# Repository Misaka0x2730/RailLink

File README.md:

# RailLink
Very compact isolated version of J-Link v9 with fully supported functions. </br>
Isolation based on ADuM4160 (USB2.0 FS isolation) and B0505S-1W (Isolated 5V/0.2A DC-DC). </br>

# Overview
Dimensions(L x W x H, millimeters): 70 x 28 x 15 (probe only); 110 x 35 x 25 (probe with connected adapter). </br>

# Probe pinout
RailLink has 10 pin 0.1"(2.54mm) connector compatible with standard ARM 10 pin connector.

<b>RailLink connector</b></br>

|Pin|Name   |Pin|Name        |
|---|-------|---|------------|
|1  |Vtref  |2  | TMS/SWDIO  |
|3  |GND    |4  | TCK/SWCLK  |
|5  |GND    |6  | TDO/SWO    |
|7  |UART RX|8  | TDI/UART TX|
|9  |GND    |10 | ~RESET     |

# Adapter pinouts
Adapter has several popular connectors: ARM 10 pin 0.05"(1.27mm), TC2030-IDC-NL  6 pin 0.1"(2.54mm), ARM 20 pin JTAG 0.1"(2.54mm), ARM 20-pin Cortex 0.05"(1.27mm). </br>
In addition, there are two custom connectors: 4 pin UART and CWF-6 (Ilya).

<b>ARM 10 pin 0.05"(1.27mm)</b></br>

|Pin|Name   |Pin|Name        |
|---|-------|---|------------|
|1  |Vtref  |2  | TMS/SWDIO  |
|3  |GND    |4  | TCK/SWCLK  |
|5  |GND    |6  | TDO/SWO    |
|7  |UART RX|8  | TDI/UART TX|
|9  |GND    |10 | ~RESET     |

</br></br><b>TC2030-IDC-NL</b></br>

|Pin|Name   |Pin|Name        |
|---|-------|---|------------|
|1  |Vtref  |2  | TMS/SWDIO  |
|3  |~RESET |4  | TCK/SWCLK  |
|5  |GND    |6  | TDO/SWO    |

</br></br><b>ARM 20 pin JTAG 0.1"(2.54mm)</b></br>

|Pin|Name        |Pin|Name |
|---|------------|---|-----|
|1  |Vtref       |2  | NC  |
|3  |NC          |4  | GND |
|5  |TDI/UART TX |6  | GND |
|7  |TMS/SWDIO   |8  | GND |
|9  |TCK/SWCLK   |10 | GND |
|11 |NC          |12 | GND |
|13 |TDO/SWO     |14 | GND |
|15 |~RESET      |16 | GND |
|17 |UART RX     |18 | GND |
|19 |NC          |20 | GND |

</br></br><b>ARM 20-pin Cortex 0.05"(1.27mm)</b></br>

|Pin|Name   |Pin|Name        |
|---|-------|---|------------|
|1  |Vtref  |2  | TMS/SWDIO  |
|3  |GND    |4  | TCK/SWCLK  |
|5  |GND    |6  | TDO/SWO    |
|7  |UART RX|8  | TDI/UART TX|
|9  |GND    |10 | ~RESET     |
|11 |GND    |12 | NC         |
|13 |GND    |14 | NC         |
|15 |GND    |16 | NC         |
|17 |GND    |18 | NC         |
|19 |GND    |20 |NC          |

</br></br><b>4 pin UART</b></br>

|Pin|Name        |
|---|------------|
|1  |Vtref       |
|2  |TDI/UART TX |
|3  |UART RX     |
|4  |GND         |

</br></br><b>CWF-6 (Ilya)</b></br>

|Pin|Name        |
|---|------------|
|1  |Vtref       |
|2  |TCK/SWCLK   |
|3  |TMS/SWDIO   |
|4  |~RESET      |
|3  |UART RX     |
|4  |GND         |

# Assembly
Most of SMD components are 0402. </br> 
Assembly should be not very difficult even with soldering iron. </br>
But paste soldering with stencil is recommended. </br>
Assembly drawing placed [here](https://github.com/Misaka0x2730/RailLink/blob/master/BOM/ibom.html). </br>
Assembly drawing should be opened in browser. </br>

# Programming
 1. Install J-Link software pack.
 2. Load the bootloader
    * <b>ST-LINK way </b>
      1. Install ST-LINK utility
      2. Connect RailLink SWD connector to ST-LINK
      3. Connect ST-LINK to PC
      4. Connect RailLink to PC
      5. Launch ST-LINK utility
      6. Load [this file](https://github.com/Kevincoooool/KS_Diy_Link/blob/master/Jlink_V9/%E5%9B%BA%E4%BB%B6%E5%8D%87%E7%BA%A7%E6%96%B9%E5%BC%8F/JLink-v9_bootloader%E5%9B%BA%E4%BB%B6/bootloader.bin)
      into MCU.
    * <b>J-Link way</b>
      1. Connect RailLink SWD connector to J-Link
      2. Connect J-Link to PC
      3. Connect RailLink to PC
      4. Start JFlashLite </br> 
      6. Select device - STM32F205RC, select interface - SWD, and speed - 100kHz </br>
      
      8. In Data file field choose [this file](https://github.com/Kevincoooool/KS_Diy_Link/blob/master/Jlink_V9/%E5%9B%BA%E4%BB%B6%E5%8D%87%E7%BA%A7%E6%96%B9%E5%BC%8F/JLink-v9_bootloader%E5%9B%BA%E4%BB%B6/bootloader.bin)
      9. Click "Program Device" button
      10. Wait until the firmware is loaded;
  3. Disconnect RailLink and JLink from PC.
  4. Connect RailLink to PC.
  5. Launch JLink.exe (JLinkExe on Linux) and agree to firmware restoring.
  6. Wait until firmware is restored.
  7. Now RailLink is almost ready for use. Type and run "Exec SetSN=xxxxxxxx", where xxxxxxxx is serial number; 
  8. <b> RailLink is ready for use! </b>
  
<b>PS. Important! </b></br> It's recommended to add following options:
  * Exec AddFeature GDB
  * Exec AddFeature RDI
  * Exec AddFeature FlashBP
  * Exec AddFeature FlashDL
  * Exec AddFeature JFlash
  * Exec AddFeature RDDI </br>
But in latest version (V6.80 at this moment) any of these commands causes "ERROR: Unknown command". </br>
You can install older version (two or more version of JLink software pack can be install on one PC) and try to execute these commands. 
For example, it's working on V6.30.

# License
 </br>
This project is licensed under a [CERN Open Hardware Licence Version 2 - Permissive](https://ohwr.org/cern_ohl_p_v2.pdf).

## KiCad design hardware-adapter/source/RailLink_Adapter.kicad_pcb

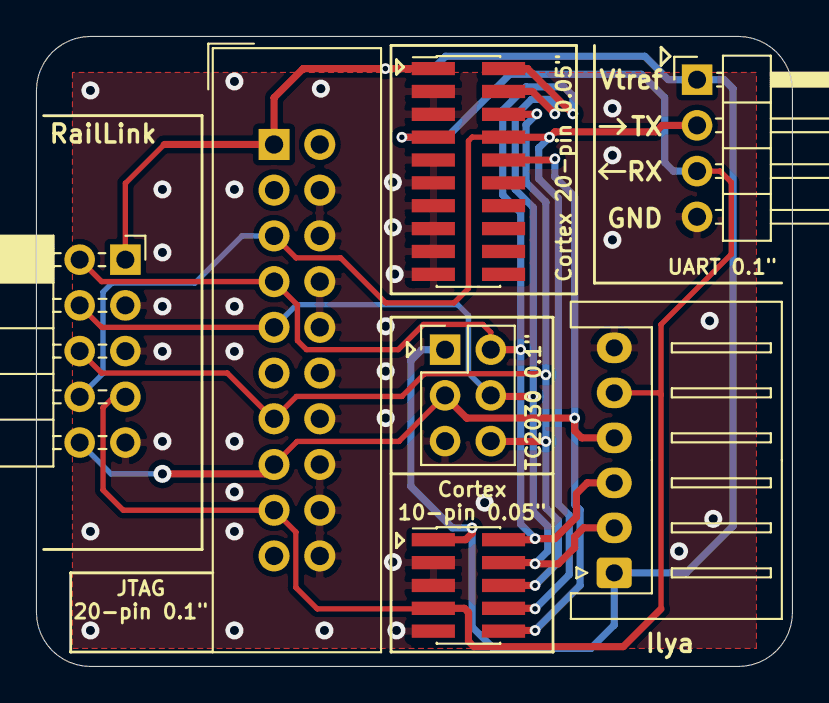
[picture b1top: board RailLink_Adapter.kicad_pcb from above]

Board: 2 copper layers, 42.0 x 35.0 mm, 7 parts (0 on the bottom side), 8 nets.

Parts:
J1: RailLink; PinSocket_2x05_P2.54mm_Horizontal
J2: 10-pin Cortex Debug; PinHeader_2x05_P1.27mm_Vertical_SMD
J3: TC2030-IDC-NL; PinHeader_2x03_P2.54mm_Vertical
J4: Standard JTAG; IDC-Header_2x10_P2.54mm_Vertical
J5: 20-pin Cortex Debug + ETM; PinHeader_2x10_P1.27mm_Vertical_SMD
J6: UART; PinHeader_1x04_P2.54mm_Horizontal
J7: Ilya; JST_XH_S6B-XH-A_1x06_P2.50mm_Horizontal

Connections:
/RXD: J1.7, J2.7, J4.17, J5.7, J6.3, J7.5
/TCK: J1.4, J2.4, J3.4, J4.9, J5.4, J7.2
/TDI: J1.8, J2.8, J4.5, J5.8, J6.2
/TDO: J1.6, J2.6, J3.6, J4.13, J5.6
/TMS: J1.2, J2.2, J3.2, J4.7, J5.2, J7.3
/Vtref: J1.1, J2.1, J3.1, J4.1, J5.1, J6.1, J7.1
/~RESET: J1.10, J2.10, J3.3, J4.15, J5.10, J7.4
GND: J1.3, J1.5, J1.9, J2.3, J2.5, J2.9, J3.5, J4.4, J4.6, J4.8, J4.10, J4.12, J4.14, J4.16, J4.18, J4.20, J5.3, J5.5, J5.9, J5.11, J5.13, J5.15, J5.17, J5.19, J6.4, J7.6

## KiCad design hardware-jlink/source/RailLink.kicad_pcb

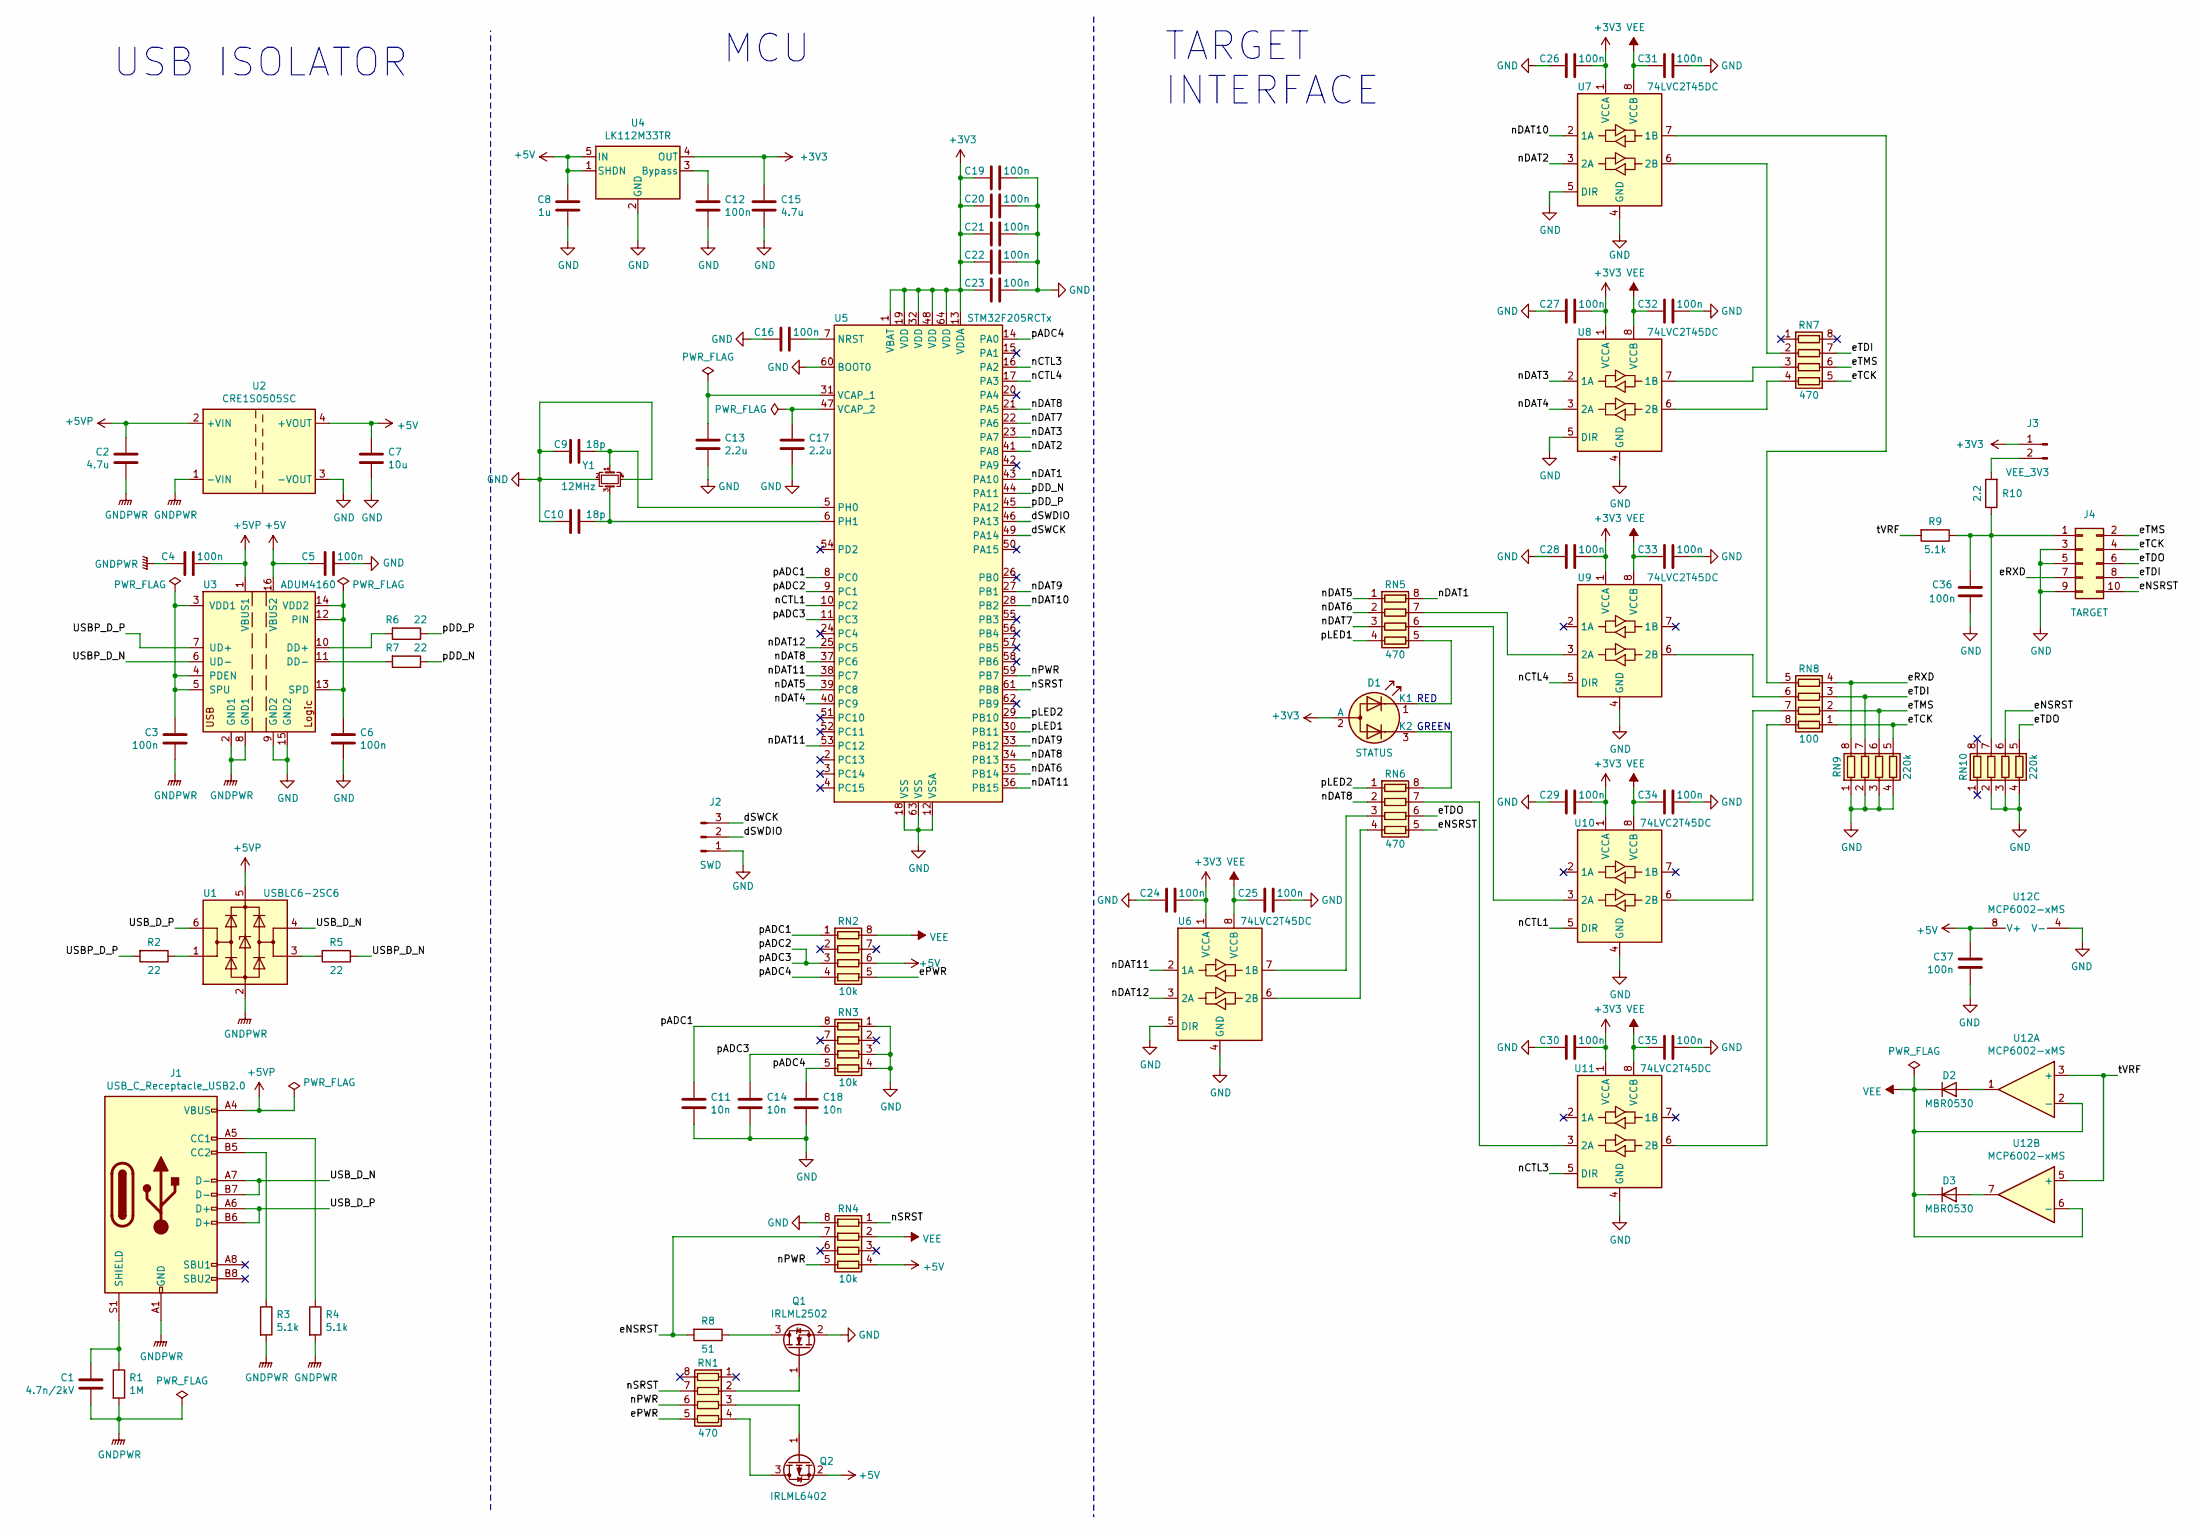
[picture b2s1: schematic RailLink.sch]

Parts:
C1: 4.7n/2kV; C_1812_4532Metric; Part Number 202S43W472KV4E
C2, C15: 4.7u; C_0603_1608Metric; Part Number CL10A475KP8NNNC
C3, C4, C5, C6, C12, C16, C19, C20, C21, C22, C23, C24, C25, C26, C27, C28, C29, C30, C31, C32, C33, C34, C35, C36, C37: 100n; C_0402_1005Metric; Part Number 0402B104K160CT
C7: 10u; C_0603_1608Metric; Part Number GRM188R61A106ME69D
C8: 1u; C_0603_1608Metric; Part Number CL10B105KP8NNNC
C9, C10: 18p; C_0402_1005Metric; Part Number C1005NP0180KGT
C11, C14, C18: 10n; C_0402_1005Metric; Part Number 0402B103K500NT
C13, C17: 2.2u; C_0603_1608Metric; Part Number CL10A225KP8NNNC
D1: STATUS; LED_D3.0mm-3; Part Number TJ-L3FYTXHMCYLC2R2G-A5
D2, D3: MBR0530; D_SOD-123; Part Number MBR0530
J1: USB_C_Receptacle_USB2.0; USB_C_Receptacle_HRO_TYPE-C-31-M-12; Part Number TYPE-C-31-M-12
J2: SWD; PinHeader_1x03_P2.54mm_Vertical; Part Number C2337
J3: VEE_3V3; PinHeader_1x02_P2.54mm_Vertical; Part Number C2337
J4: TARGET; IDC-Header_2x05_P2.54mm_Horizontal; Part Number C9140
Q1: IRLML2502; SOT-23; Part Number IRLML2502
Q2: IRLML6402; SOT-23; Part Number IRLML6402
R1: 1M; R_1206_3216Metric; Part Number 1206W4J0105T5E
R2, R5, R6, R7: 22; R_0402_1005Metric; Part Number 0402WGF220JTCE
R3, R4, R9: 5.1k; R_0402_1005Metric; Part Number 0402WGJ0512TCE
R8: 51; R_0402_1005Metric; Part Number 0402WGJ0510TCE
R10: 2.2; R_0402_1005Metric; Part Number RC0402FR-071KL
RN1, RN5, RN6, RN7: 470; R_Array_Concave_4x0603; Part Number 4D03WGJ0471T5E
RN2, RN3, RN4: 10k; R_Array_Concave_4x0603; Part Number 4D03WGJ0103T5E
RN8: 100; R_Array_Concave_4x0603; Part Number 4D03WGJ0101T5E
RN9, RN10: 220k; R_Array_Concave_4x0603; Part Number 4D03WGJ0224T5E
U1: USBLC6-2SC6; SOT-23-6; Part Number USBLC6-2SC6
U2: CRE1S0505SC; Converter_DCDC_muRata_CRE1xxxxxxSC_THT; Part Number B0505S-1W
U3: ADUM4160; SOIC-16W_7.5x10.3mm_P1.27mm; Part Number ADUM4160BRWZ-RL
U4: LK112M33TR; SOT-23-5; Part Number LK112M33TR
U5: STM32F205RCTx; LQFP-64_10x10mm_P0.5mm; Part Number STM32F205RCT6
U6, U7, U8, U9, U10, U11: 74LVC2T45DC; VSSOP-8_2.3x2mm_P0.5mm; Part Number SN74LVC2T45DCUR
U12: MCP6002-xMS; VSSOP-8_3.0x3.0mm_P0.65mm; Part Number MCP6002-I/MS
Y1: 12MHz; Crystal_SMD_3225-4Pin_3.2x2.5mm; Part Number X322512MSB4SI

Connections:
+3V3: C15.2, C19.2, C20.2, C21.2, C22.2, C23.2, C24.1, C26.1, C27.1, C28.1, C29.1, C30.1, D1.2 (A), J3.1, U4.4 (OUT), U5.1 (VBAT), U5.13 (VDDA), U5.19 (VDD), U5.32 (VDD), U5.48 (VDD), U5.64 (VDD), U6.1 (VCCA), U7.1 (VCCA), U8.1 (VCCA), U9.1 (VCCA), U10.1 (VCCA), U11.1 (VCCA)
+5V: C5.1, C7.2, C8.2, C37.1, Q2.2 (S), RN2.6 (R3.2), RN4.4 (R4.1), U2.4 (+VOUT), U3.16 (VBUS2), U4.1 (SHDN), U4.5 (IN), U12.8 (V+)
+5VP: C2.2, C4.2, J1.A4 (VBUS), J1.A9 (VBUS), J1.B4 (VBUS), J1.B9 (VBUS), U1.5 (VBUS), U2.2 (+VIN), U3.1 (VBUS1)
/USBP_D_N: R5.1, U3.6 (UD-)
/USBP_D_P: R2.2, U3.7 (UD+)
/USB_D_N: J1.A7 (D-), J1.B7 (D-), U1.4 (I/O2)
/USB_D_P: J1.A6 (D+), J1.B6 (D+), U1.6 (I/O1)
/dSWCK: J2.3, U5.49 (PA14)
/dSWDIO: J2.2, U5.46 (PA13)
/eNSRST: J4.10, R8.2, RN4.7 (R2.2), RN6.5 (R4.2), RN10.6 (R3.2)
/ePWR: RN1.5 (R4.2), RN2.5 (R4.2)
/eRXD: J4.7, RN8.4 (R4.1), RN9.8 (R1.2)
/eTCK: J4.4, RN7.5 (R4.2), RN8.1 (R1.1), RN9.5 (R4.2)
/eTDI: J4.8, RN7.7 (R2.2), RN8.3 (R3.1), RN9.7 (R2.2)
/eTDO: J4.6, RN6.6 (R3.2), RN10.5 (R4.2)
/eTMS: J4.2, RN7.6 (R3.2), RN8.2 (R2.1), RN9.6 (R3.2)
/nCTL1: U5.10 (PC2), U10.5 (DIR)
/nCTL3: U5.16 (PA2), U11.5 (DIR)
/nCTL4: U5.17 (PA3), U9.5 (DIR)
/nDAT1: RN5.8 (R1.2), U5.43 (PA10)
/nDAT2: U5.41 (PA8), U7.3 (2A)
/nDAT3: U5.23 (PA7), U8.2 (1A)
/nDAT4: U5.40 (PC9), U8.3 (2A)
/nDAT5: RN5.1 (R1.1), U5.39 (PC8)
/nDAT6: RN5.2 (R2.1), U5.35 (PB14)
/nDAT7: RN5.3 (R3.1), U5.22 (PA6)
/nDAT8: RN6.2 (R2.1), U5.21 (PA5), U5.34 (PB13), U5.37 (PC6)
/nDAT9: U5.27 (PB1), U5.33 (PB12)
/nDAT10: U5.28 (PB2), U7.2 (1A)
/nDAT11: U5.36 (PB15), U5.38 (PC7), U5.53 (PC12), U6.2 (1A)
/nDAT12: U5.25 (PC5), U6.3 (2A)
/nPWR: RN1.6 (R3.2), RN4.5 (R4.2), U5.59 (PB7)
/nSRST: RN1.7 (R2.2), RN4.1 (R1.1), U5.61 (PB8)
/pADC1: C11.1, RN2.1 (R1.1), RN3.8 (R1.2), U5.8 (PC0)
/pADC2: C14.1, RN2.3 (R3.1), RN3.6 (R3.2), U5.9 (PC1), U5.11 (PC3)
/pADC4: C18.1, RN2.4 (R4.1), RN3.5 (R4.2), U5.14 (PA0)
/pDD_N: R7.1, U5.44 (PA11)
/pDD_P: R6.1, U5.45 (PA12)
/pLED1: RN5.4 (R4.1), U5.30 (PB11)
/pLED2: RN6.1 (R1.1), U5.29 (PB10)
/tVRF: R9.2, U12.3 (+), U12.5 (+)
GND: C5.2, C6.1, C7.1, C8.1, C9.2, C10.1, C11.2, C12.1, C13.2, C14.2, C15.1, C16.2, C17.2, C18.2, C19.1, C20.1, C21.1, C22.1, C23.1, C24.2, C25.1, C26.2, C27.2, C28.2, C29.2, C30.2, C31.1, C32.1, C33.1, C34.1, C35.1, C36.2, C37.2, J2.1, J4.3, J4.5, J4.9, Q1.2 (S), RN3.1 (R1.1), RN3.3 (R3.1), RN3.4 (R4.1), RN4.8 (R1.2), RN9.1 (R1.1), RN9.2 (R2.1), RN9.3 (R3.1), RN9.4 (R4.1), RN10.2 (R2.1), RN10.3 (R3.1), RN10.4 (R4.1), U2.3 (-VOUT), U3.9 (GND2), U3.15 (GND2), U4.2 (GND), U5.12 (VSSA), U5.18 (VSS), U5.60 (BOOT0), U5.63 (VSS), U6.4 (GND), U6.5 (DIR), U7.4 (GND), U7.5 (DIR), U8.4 (GND), U8.5 (DIR), U9.4 (GND), U10.4 (GND), U11.4 (GND), U12.4 (V-), Y1.2, Y1.4
GNDPWR: C1.1, C2.1, C3.1, C4.1, J1.A1 (GND), J1.A12 (GND), J1.B1 (GND), J1.B12 (GND), R1.2, R3.2, R4.2, U1.2 (GND), U2.1 (-VIN), U3.2 (GND1), U3.8 (GND1)
unnamed: C1.2, J1.S1 (SHIELD), R1.1
unnamed: C3.2, U3.3 (VDD1), U3.4 (PDEN), U3.5 (SPU)
unnamed: C6.2, U3.12 (PIN), U3.13 (SPD), U3.14 (VDD2)
unnamed: C9.1, U5.5 (PH0), Y1.1
unnamed: C10.2, U5.6 (PH1), Y1.3
unnamed: C12.2, U4.3 (Bypass)
unnamed: C13.1, U5.31 (VCAP_1)
unnamed: C16.1, U5.7 (NRST)
unnamed: C17.1, U5.47 (VCAP_2)
unnamed: C36.1, J4.1, R9.1, R10.1, RN10.7 (R2.2)
unnamed: D1.1 (K1), RN5.5 (R4.2)
unnamed: D1.3 (K2), RN6.8 (R1.2)
unnamed: D2.2 (A), U12.1
unnamed: D3.2 (A), U12.7
unnamed: J1.A5 (CC1), R4.1
unnamed: J1.B5 (CC2), R3.1
unnamed: J3.2, R10.2
unnamed: Q1.1 (G), RN1.2 (R2.1)
unnamed: Q1.3 (D), R8.1
unnamed: Q2.1 (G), RN1.3 (R3.1)
unnamed: Q2.3 (D), RN1.4 (R4.1)
unnamed: R2.1, U1.1 (I/O1)
unnamed: R5.2, U1.3 (I/O2)
unnamed: R6.2, U3.10 (DD+)
unnamed: R7.2, U3.11 (DD-)
unnamed: RN5.6 (R3.2), U10.3 (2A)
unnamed: RN5.7 (R2.2), U9.3 (2A)
unnamed: RN6.3 (R3.1), U6.7 (1B)
unnamed: RN6.4 (R4.1), U6.6 (2B)
unnamed: RN6.7 (R2.2), U11.3 (2A)
unnamed: RN7.2 (R2.1), U7.6 (2B)
unnamed: RN7.3 (R3.1), U8.7 (1B)
unnamed: RN7.4 (R4.1), U8.6 (2B)
unnamed: RN8.5 (R4.2), U7.7 (1B)
unnamed: RN8.6 (R3.2), U9.6 (2B)
unnamed: RN8.7 (R2.2), U10.6 (2B)
unnamed: RN8.8 (R1.2), U11.6 (2B)
VEE: C25.2, C31.2, C32.2, C33.2, C34.2, C35.2, D2.1 (K), D3.1 (K), RN2.8 (R1.2), RN4.2 (R2.1), U6.8 (VCCB), U7.8 (VCCB), U8.8 (VCCB), U9.8 (VCCB), U10.8 (VCCB), U11.8 (VCCB), U12.2 (-), U12.6 (-)

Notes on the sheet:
USB ISOLATOR
MCU
TARGET INTERFACE
RED
GREEN

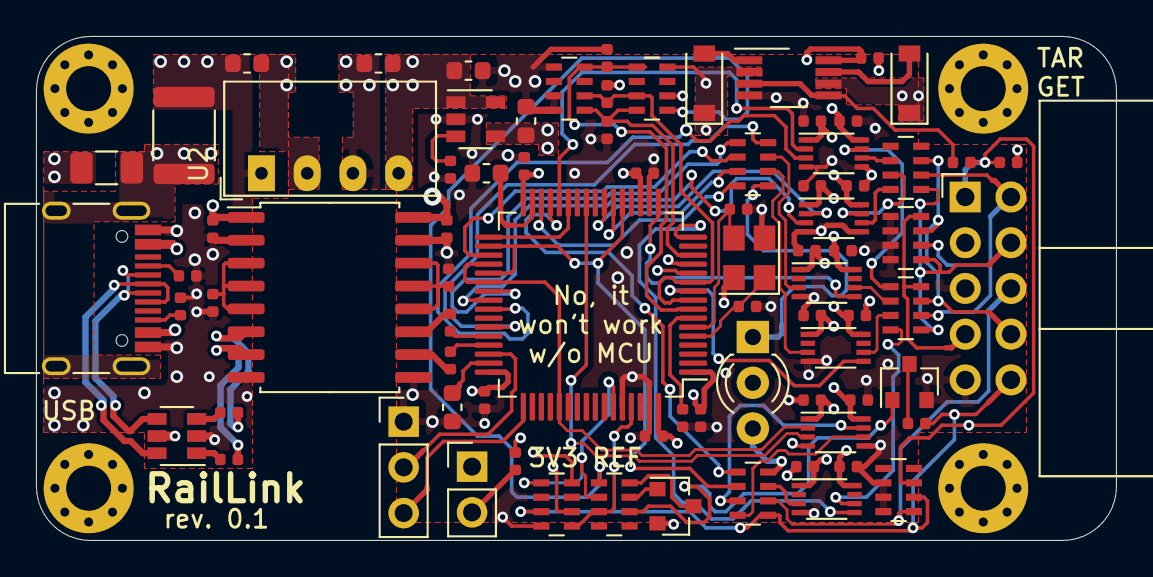
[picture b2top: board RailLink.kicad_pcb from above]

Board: 4 copper layers, 60.0 x 28.0 mm, 79 parts (0 on the bottom side), 81 nets.

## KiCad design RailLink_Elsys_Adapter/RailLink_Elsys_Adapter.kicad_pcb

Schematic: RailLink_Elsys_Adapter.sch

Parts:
J1: UART; IDC-Header_2x03_P2.54mm_Vertical
J2: RailLink; IDC-Header_2x06_P2.54mm_Horizontal
J3: CAL; PinHeader_1x02_P2.54mm_Vertical
J4: Target; PinHeader_1x07_P2.54mm_Vertical
JP1: BOOT; PinHeader_1x02_P2.54mm_Vertical

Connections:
/RTCCR: J3.1, J4.3
/RXD: J1.5, J2.7
/TCK: J2.4, J4.7
/TMS: J2.2, J4.5
/TXD: J1.3, J2.8
/Vtref: J1.2, J2.1, J4.2, JP1.2
/~RESET: J1.1, J2.10, J4.1
GND: J1.4, J2.3, J2.5, J2.9, J3.2, J4.4
unnamed: J1.6, JP1.1

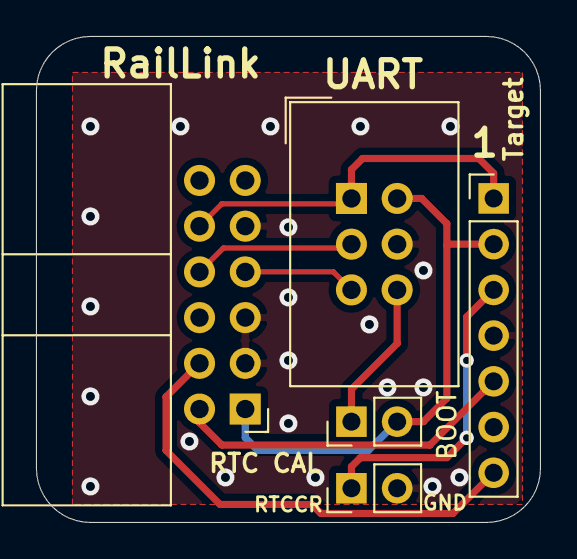
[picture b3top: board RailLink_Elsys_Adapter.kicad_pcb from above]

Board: 2 copper layers, 28.0 x 27.0 mm, 5 parts (0 on the bottom side), 9 nets.

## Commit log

2020-04-26 Initial commit. Release first pcb revision.
2020-04-26 Added short-circuit protection on tVRF net
2020-04-26 Added STEP file for PCB
2020-04-26 Added STEP file for USB Type-C connector
2020-04-28 1. Increased clearance from USB Type-C to board edge. 2. 2 status LEDs changed to single 3mm THT.
2020-04-28 Added missed files
2020-04-28 Some minor changes before PCB ordering
2020-04-28 Added bottom sikscreen layer
2020-05-01 Added CERN-OHL-P licence
2020-07-18 Changed op amp to MCP6002 and R10 value to 1k. Added component list for probe and adapter.
2020-07-19 Added 3D and assembly images
2020-07-19 Added jflashlite and jlink images
2020-07-19 Added adapter 3D image
2020-07-20 Swapped led's cathodes. Updated component availability
2020-07-22 Add adapter connectors images
2020-07-22 Update README.md
    Added pinout.
2020-09-05 Fixed R10 value (1kOhm -> 2.2Ohm)
2020-09-05 Added Elsys adapter
2020-09-22 Fixed B0505 footprint height, fixed Gerber grid origin, added solder paste Gerber files.
2020-09-24 docs: Transferred image files from the project to the hosting. Formatted project description
2020-09-24 refactor: Optimized the project structure. Created folders for different items
2020-09-24 new: Added source files of the device case project to SolidWorks 2019
2020-11-19 fix: Внес правки по корпусу после изготовления прототипа
    - сдвинул отверстие под светодиод на 0.25 мм и уменьшил его
    диаметр на 0.1 мм до 3.1 мм для более плотного расположения;
    - сделал радиаусы кратными 2 мм для снижения стоимости работ
    по фрезеровке корпуса
2021-09-06 Update README.md
    Updated the bootloader download link.
